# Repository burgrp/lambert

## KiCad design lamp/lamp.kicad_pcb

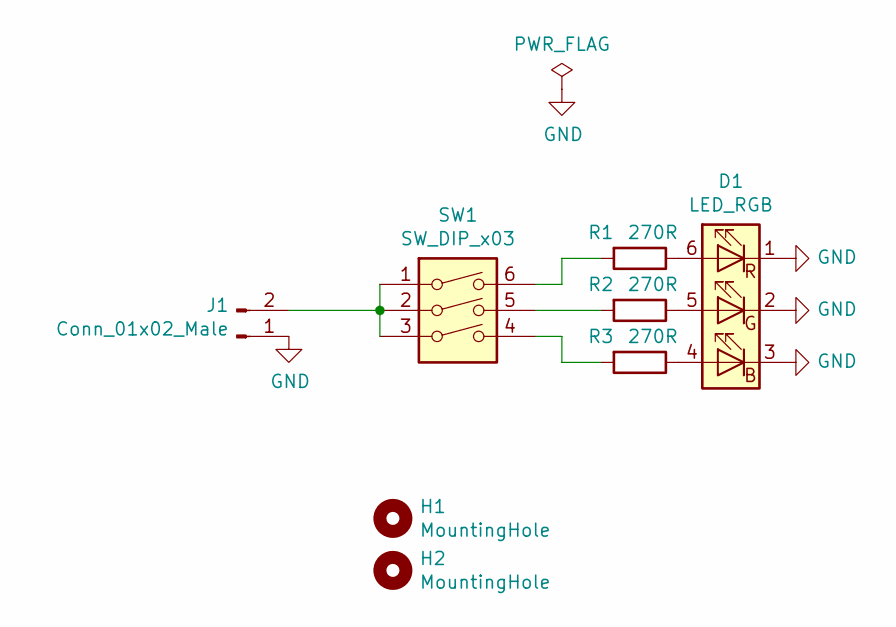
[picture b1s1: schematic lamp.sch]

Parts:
D1: LED_RGB; LED_RGB_5050-6
H1, H2: MountingHole; MountingHole_3.7mm
J1: Conn_01x02_Male; XT60PW-M
R1, R2, R3: 270R; R_0805_2012Metric_Pad1.15x1.40mm_HandSolder
SW1: SW_DIP_x03; SW_DIP_SPSTx03_Slide_9.78x9.8mm_W7.62mm_P2.54mm

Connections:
GND: D1.1 (RK), D1.2 (GK), D1.3 (BK), J1.1
unnamed: D1.4 (BA), R3.1
unnamed: D1.5 (GA), R2.1
unnamed: D1.6 (RA), R1.1
unnamed: J1.2, SW1.1, SW1.2, SW1.3
unnamed: R1.2, SW1.6
unnamed: R2.2, SW1.5
unnamed: R3.2, SW1.4

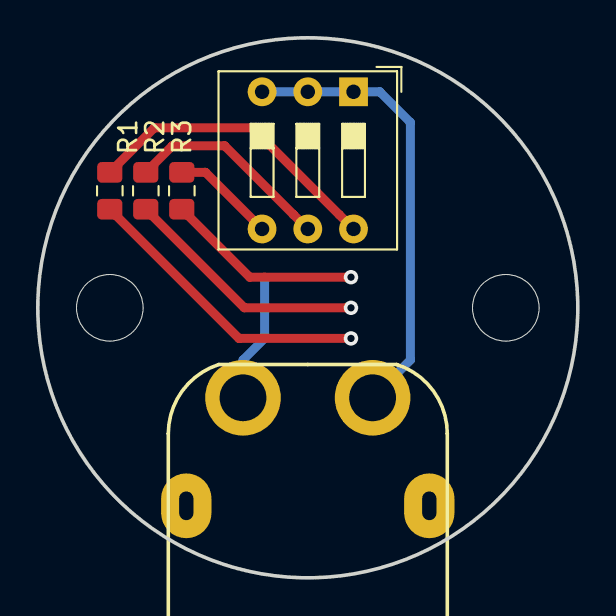
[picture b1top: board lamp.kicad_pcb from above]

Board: 2 copper layers, 30.0 x 30.0 mm, 8 parts (1 on the bottom side), 8 nets.

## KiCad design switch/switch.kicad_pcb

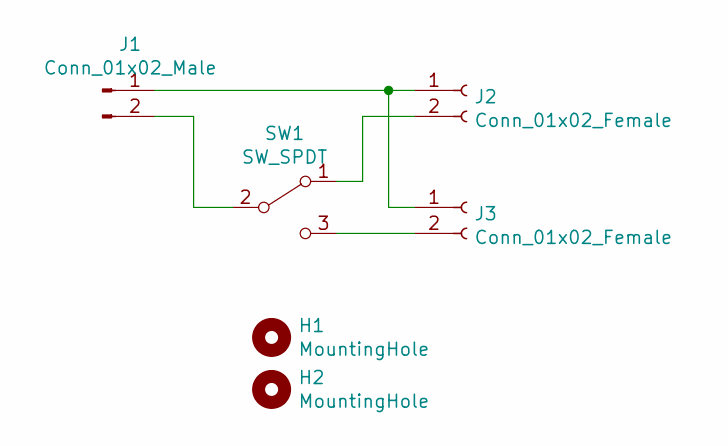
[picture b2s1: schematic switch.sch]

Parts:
H1, H2: MountingHole; MountingHole_3.7mm
J1: Conn_01x02_Male; XT60PW-M
J2, J3: Conn_01x02_Female; XT60PW-F
SW1: SW_SPDT; TS-01

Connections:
unnamed: J1.1, J2.1, J3.1
unnamed: J1.2, SW1.2 (B)
unnamed: J2.2, SW1.1 (A)
unnamed: J3.2, SW1.3 (C)

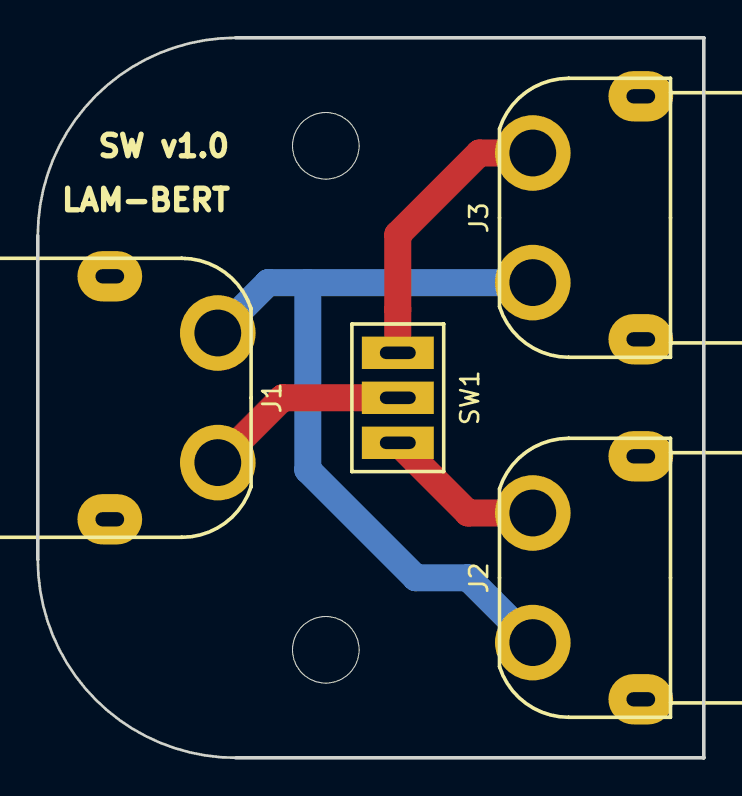
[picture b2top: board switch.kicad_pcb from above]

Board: 2 copper layers, 37.0 x 40.0 mm, 6 parts (0 on the bottom side), 4 nets.

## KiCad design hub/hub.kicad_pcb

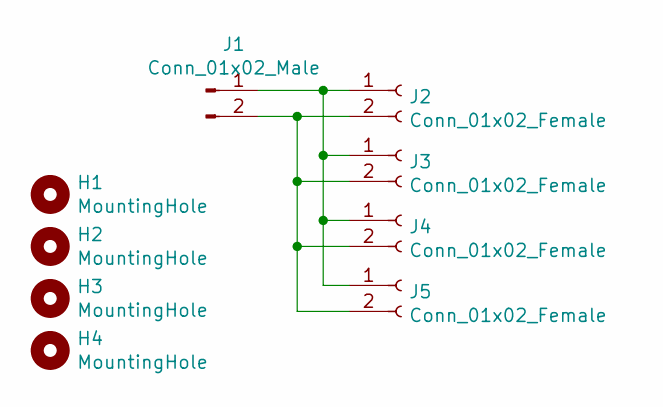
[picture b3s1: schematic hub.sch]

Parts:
H1, H2, H3, H4: MountingHole; MountingHole_3.7mm
J1: Conn_01x02_Male; XT60PW-M
J2, J3, J4, J5: Conn_01x02_Female; XT60PB-F

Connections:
unnamed: J1.1, J2.1, J3.1, J4.1, J5.1
unnamed: J1.2, J2.2, J3.2, J4.2, J5.2

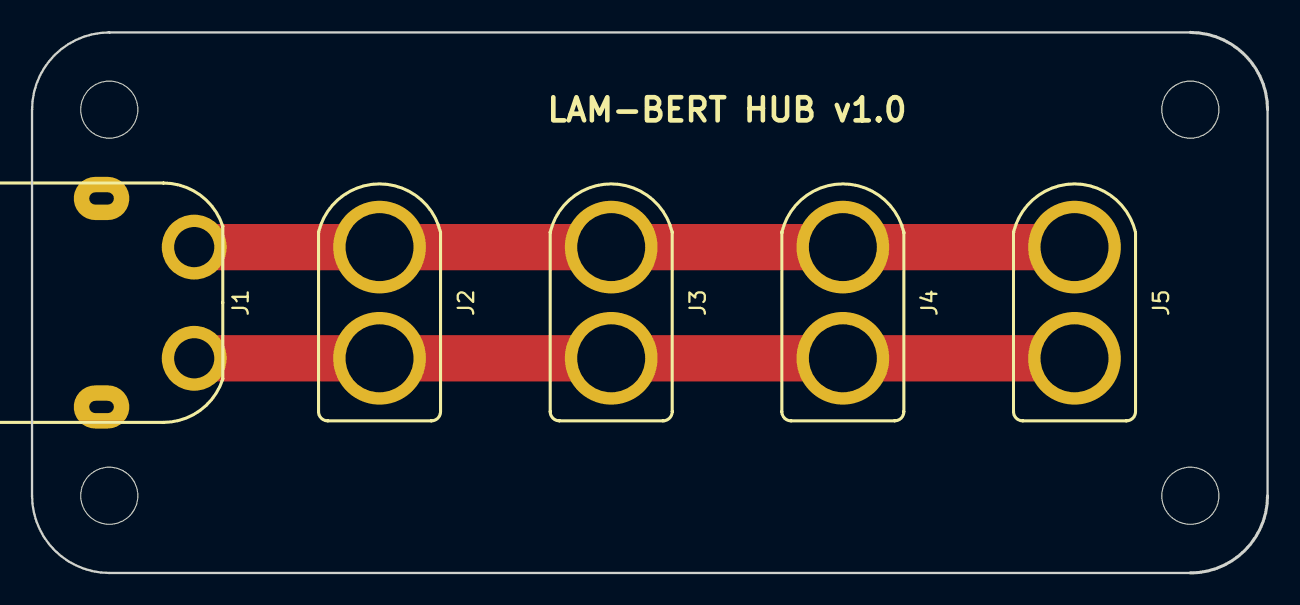
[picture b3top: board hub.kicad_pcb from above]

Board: 2 copper layers, 80.0 x 35.0 mm, 9 parts (0 on the bottom side), 2 nets.
